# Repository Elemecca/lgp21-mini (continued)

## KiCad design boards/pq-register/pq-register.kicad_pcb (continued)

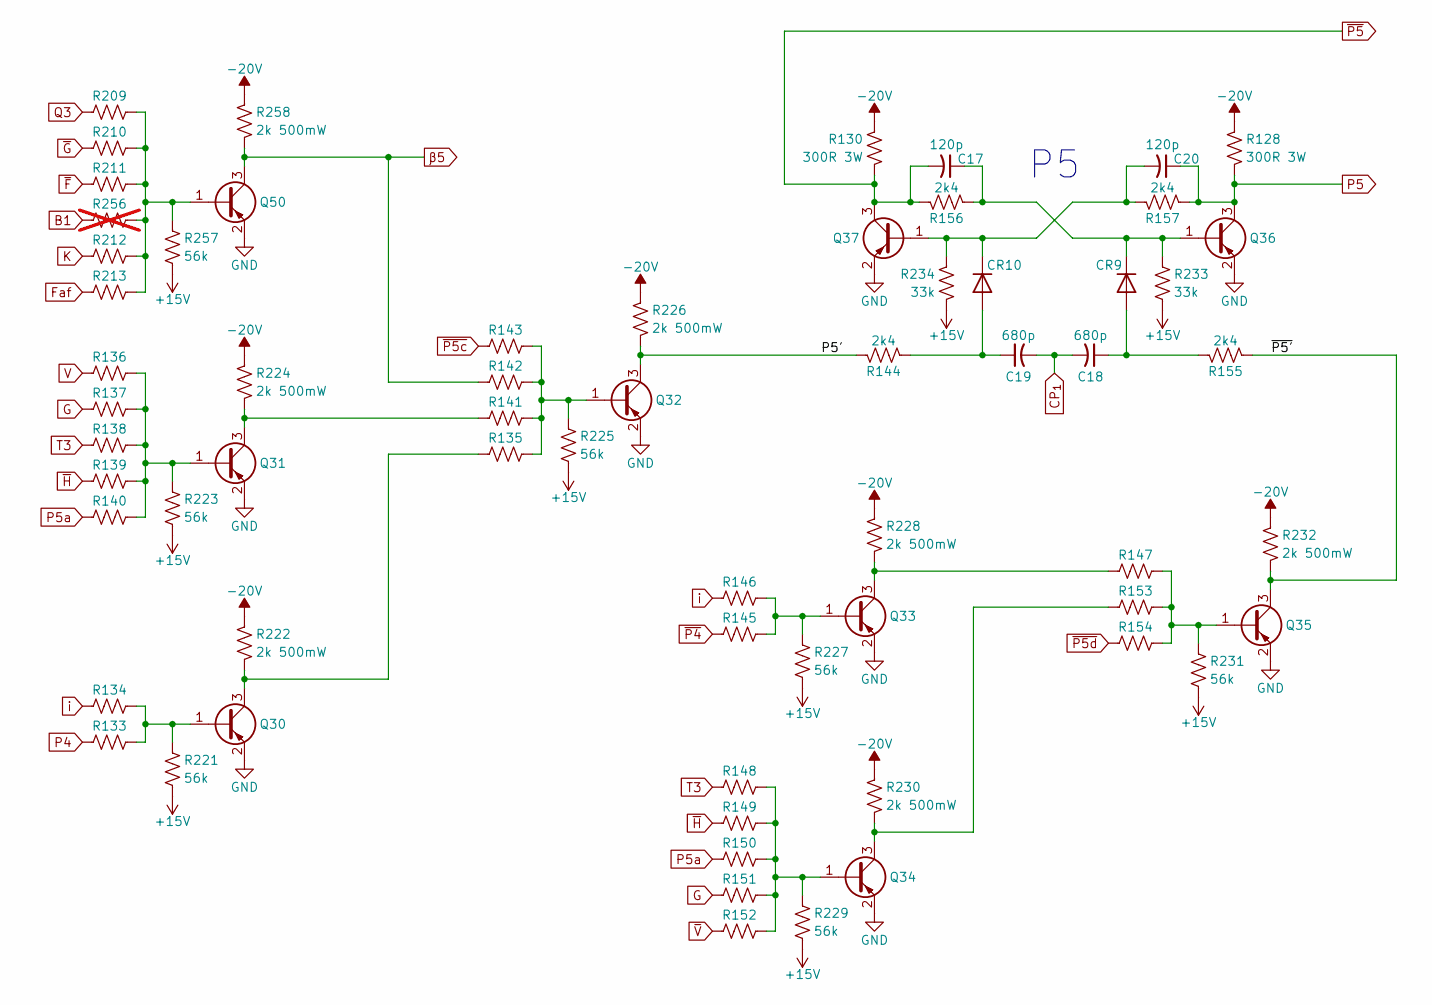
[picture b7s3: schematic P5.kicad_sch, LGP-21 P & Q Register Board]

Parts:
C17, C20: 120p; C_0402_1005Metric
C18, C19: 680p; C_0402_1005Metric
CR9, CR10: 1N5819WS; D_SOD-323
Q30, Q31, Q32, Q33, Q34, Q35, Q36, Q37, Q50: MMBT5401; SOT-23
R128, R130: 300R 3W; R_Axial_DIN0516_L15.5mm_D5.0mm_P20.32mm_Horizontal
R133, R134, R135, R136, R137, R138, R139, R140, R141, R142, R143, R145, R146, R147, R148, R149, R150, R151, R152, R153, R154, R209, R210, R211, R212, R213: 15k; R_0402_1005Metric
R144, R155, R156, R157: 2k4; R_0402_1005Metric
R221, R223, R225, R227, R229, R231, R257: 56k; R_0402_1005Metric
R222, R224, R226, R228, R230, R232, R258: 2k 500mW; R_1210_3225Metric
R233, R234: 33k; R_0402_1005Metric
R256: 15k; R_0402_1005Metric; not fitted

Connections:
+15V: R221.2, R223.2, R225.2, R227.2, R229.2, R231.2, R233.2, R234.2, R257.2; also elsewhere on the board
-20V: R128.1, R130.1, R222.1, R224.1, R226.1, R228.1, R230.1, R232.1, R258.1; also elsewhere on the board
/P5/P5': Q32.3 (C), R144.1, R226.2
/P5/~P5': Q35.3 (C), R155.2, R232.2
B1: R256.1; also elsewhere on the board
CP_{1}: C18.2, C19.2; also elsewhere on the board
Faf: R213.1; also elsewhere on the board
G: R137.1, R151.1; also elsewhere on the board
GND: Q30.2 (E), Q31.2 (E), Q32.2 (E), Q33.2 (E), Q34.2 (E), Q35.2 (E), Q36.2 (E), Q37.2 (E), Q50.2 (E); also elsewhere on the board
K: R212.1; also elsewhere on the board
unnamed: C18.1, CR9.2 (A), R155.1
unnamed: C17.1, CR9.1 (K), Q36.1 (B), R156.2, R233.1
unnamed: C19.1, CR10.2 (A), R144.2
unnamed: C20.2, CR10.1 (K), Q37.1 (B), R157.1, R234.1
unnamed: Q30.1 (B), R133.2, R134.2, R221.1
unnamed: Q30.3 (C), R135.1, R222.2
unnamed: Q31.1 (B), R136.2, R137.2, R138.2, R139.2, R140.2, R223.1
unnamed: Q31.3 (C), R141.1, R224.2
unnamed: Q32.1 (B), R135.2, R141.2, R142.2, R143.2, R225.1
unnamed: Q33.1 (B), R145.2, R146.2, R227.1
unnamed: Q33.3 (C), R147.1, R228.2
unnamed: Q34.1 (B), R148.2, R149.2, R150.2, R151.2, R152.2, R229.1
unnamed: Q34.3 (C), R153.1, R230.2
unnamed: Q35.1 (B), R147.2, R153.2, R154.2, R231.1
unnamed: Q50.1 (B), R209.2, R210.2, R211.2, R212.2, R213.2, R256.2, R257.1
P4: R133.1; also elsewhere on the board
P5: C20.1, Q36.3 (C), R128.2, R157.2; also elsewhere on the board
P5a: R140.1, R150.1; also elsewhere on the board
Q3: R209.1; also elsewhere on the board
T3: R138.1, R148.1; also elsewhere on the board
V: R136.1; also elsewhere on the board
i: R134.1, R146.1; also elsewhere on the board
~F: R211.1; also elsewhere on the board
~G: R210.1; also elsewhere on the board
~H: R139.1, R149.1; also elsewhere on the board
~P4: R145.1; also elsewhere on the board
~P5c: R143.1; also elsewhere on the board
~P5d: R154.1; also elsewhere on the board
~P5: C17.2, Q37.3 (C), R130.2, R156.1; also elsewhere on the board
~V: R152.1; also elsewhere on the board
β5: Q50.3 (C), R142.1, R258.2

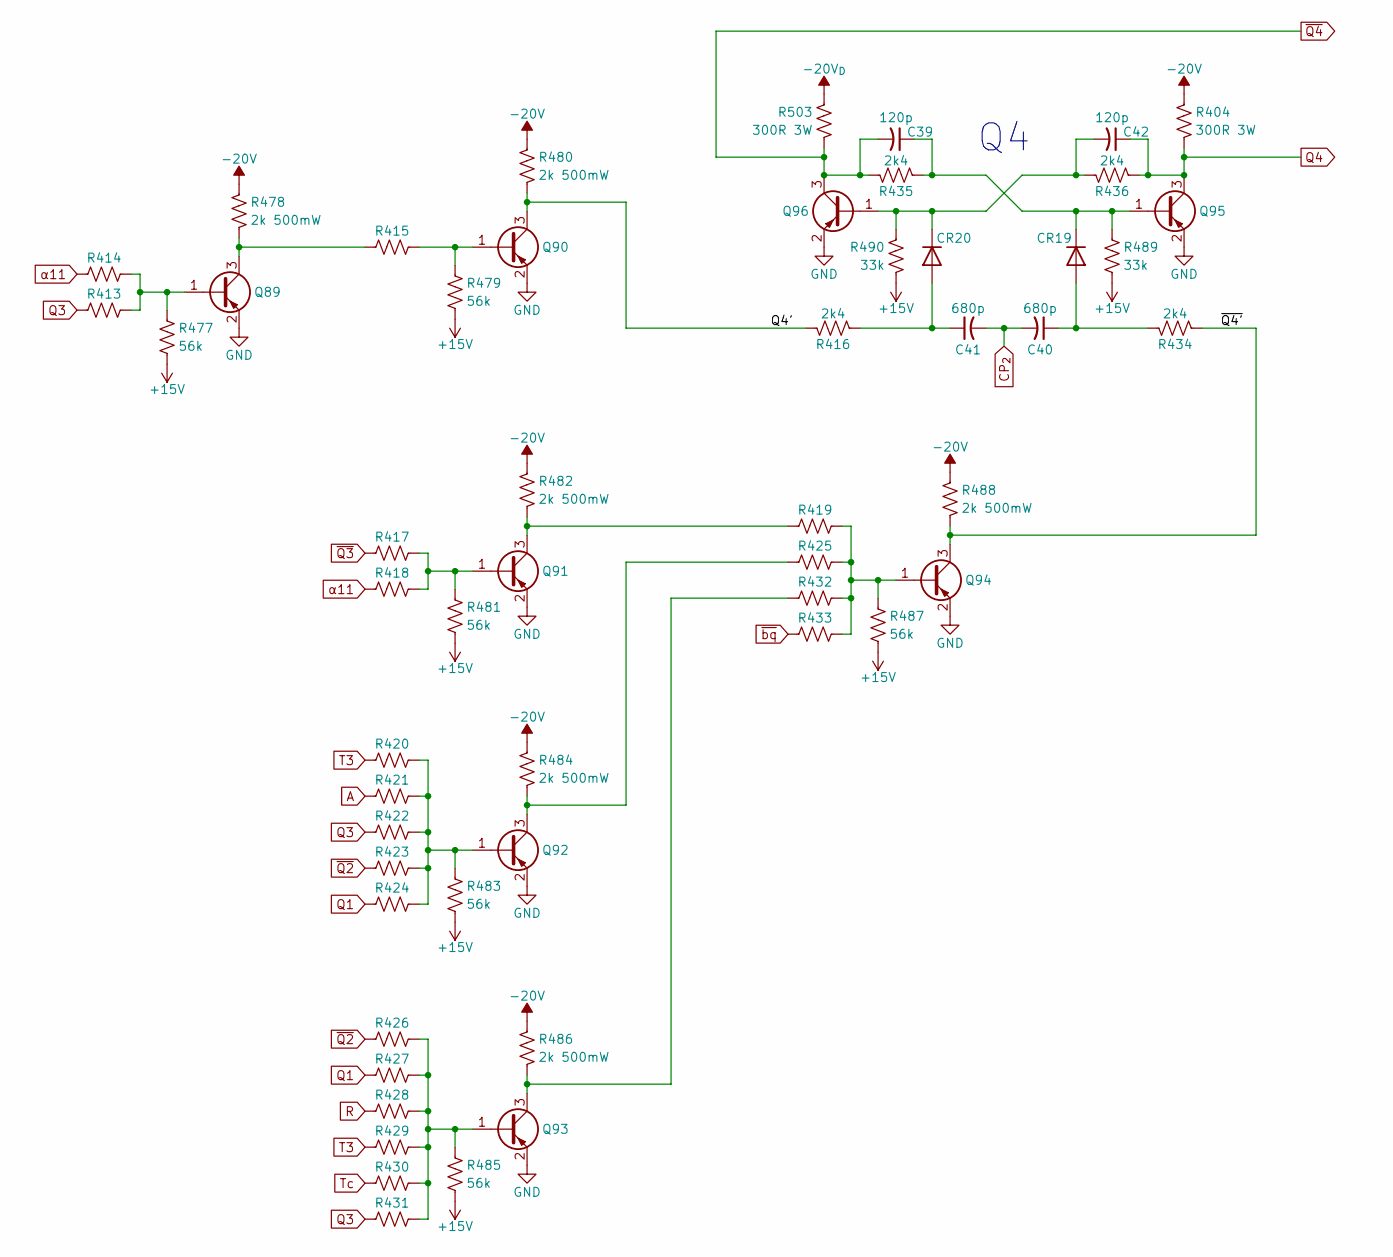
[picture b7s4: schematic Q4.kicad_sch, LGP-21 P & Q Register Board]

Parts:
C39, C42: 120p; C_0402_1005Metric
C40, C41: 680p; C_0402_1005Metric
CR19, CR20: 1N5819WS; D_SOD-323
Q89, Q90, Q91, Q92, Q93, Q94, Q95, Q96: MMBT5401; SOT-23
R404, R503: 300R 3W; R_Axial_DIN0516_L15.5mm_D5.0mm_P20.32mm_Horizontal
R413, R414, R415, R417, R418, R419, R420, R421, R422, R423, R424, R425, R426, R427, R428, R429, R430, R431, R432, R433: 15k; R_0402_1005Metric
R416, R434, R435, R436: 2k4; R_0402_1005Metric
R477, R479, R481, R483, R485, R487: 56k; R_0402_1005Metric
R478, R480, R482, R484, R486, R488: 2k 500mW; R_1210_3225Metric
R489, R490: 33k; R_0402_1005Metric

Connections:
+15V: R477.2, R479.2, R481.2, R483.2, R485.2, R487.2, R489.2, R490.2; also elsewhere on the board
-20V: R404.1, R478.1, R480.1, R482.1, R484.1, R486.1, R488.1; also elsewhere on the board
-20V_{D}: R503.1; also elsewhere on the board
/Q4/Q4': Q90.3 (C), R416.1, R480.2
/Q4/~Q4': Q94.3 (C), R434.2, R488.2
A: R421.1; also elsewhere on the board
CP_{2}: C40.2, C41.2; also elsewhere on the board
GND: Q89.2 (E), Q90.2 (E), Q91.2 (E), Q92.2 (E), Q93.2 (E), Q94.2 (E), Q95.2 (E), Q96.2 (E); also elsewhere on the board
unnamed: C40.1, CR19.2 (A), R434.1
unnamed: C39.1, CR19.1 (K), Q95.1 (B), R435.2, R489.1
unnamed: C41.1, CR20.2 (A), R416.2
unnamed: C42.2, CR20.1 (K), Q96.1 (B), R436.1, R490.1
unnamed: Q89.1 (B), R413.2, R414.2, R477.1
unnamed: Q89.3 (C), R415.1, R478.2
unnamed: Q90.1 (B), R415.2, R479.1
unnamed: Q91.1 (B), R417.2, R418.2, R481.1
unnamed: Q91.3 (C), R419.1, R482.2
unnamed: Q92.1 (B), R420.2, R421.2, R422.2, R423.2, R424.2, R483.1
unnamed: Q92.3 (C), R425.1, R484.2
unnamed: Q93.1 (B), R426.2, R427.2, R428.2, R429.2, R430.2, R431.2, R485.1
unnamed: Q93.3 (C), R432.1, R486.2
unnamed: Q94.1 (B), R419.2, R425.2, R432.2, R433.2, R487.1
Q1: R424.1, R427.1; also elsewhere on the board
Q3: R413.1, R422.1, R431.1; also elsewhere on the board
Q4: C42.1, Q95.3 (C), R404.2, R436.2; also elsewhere on the board
R: R428.1; also elsewhere on the board
T3: R420.1, R429.1; also elsewhere on the board
Tc: R430.1; also elsewhere on the board
~Q2: R423.1, R426.1; also elsewhere on the board
~Q3: R417.1; also elsewhere on the board
~Q4: C39.2, Q96.3 (C), R435.1, R503.2; also elsewhere on the board
~bq: R433.1; also elsewhere on the board
α11: R414.1, R418.1; also elsewhere on the board

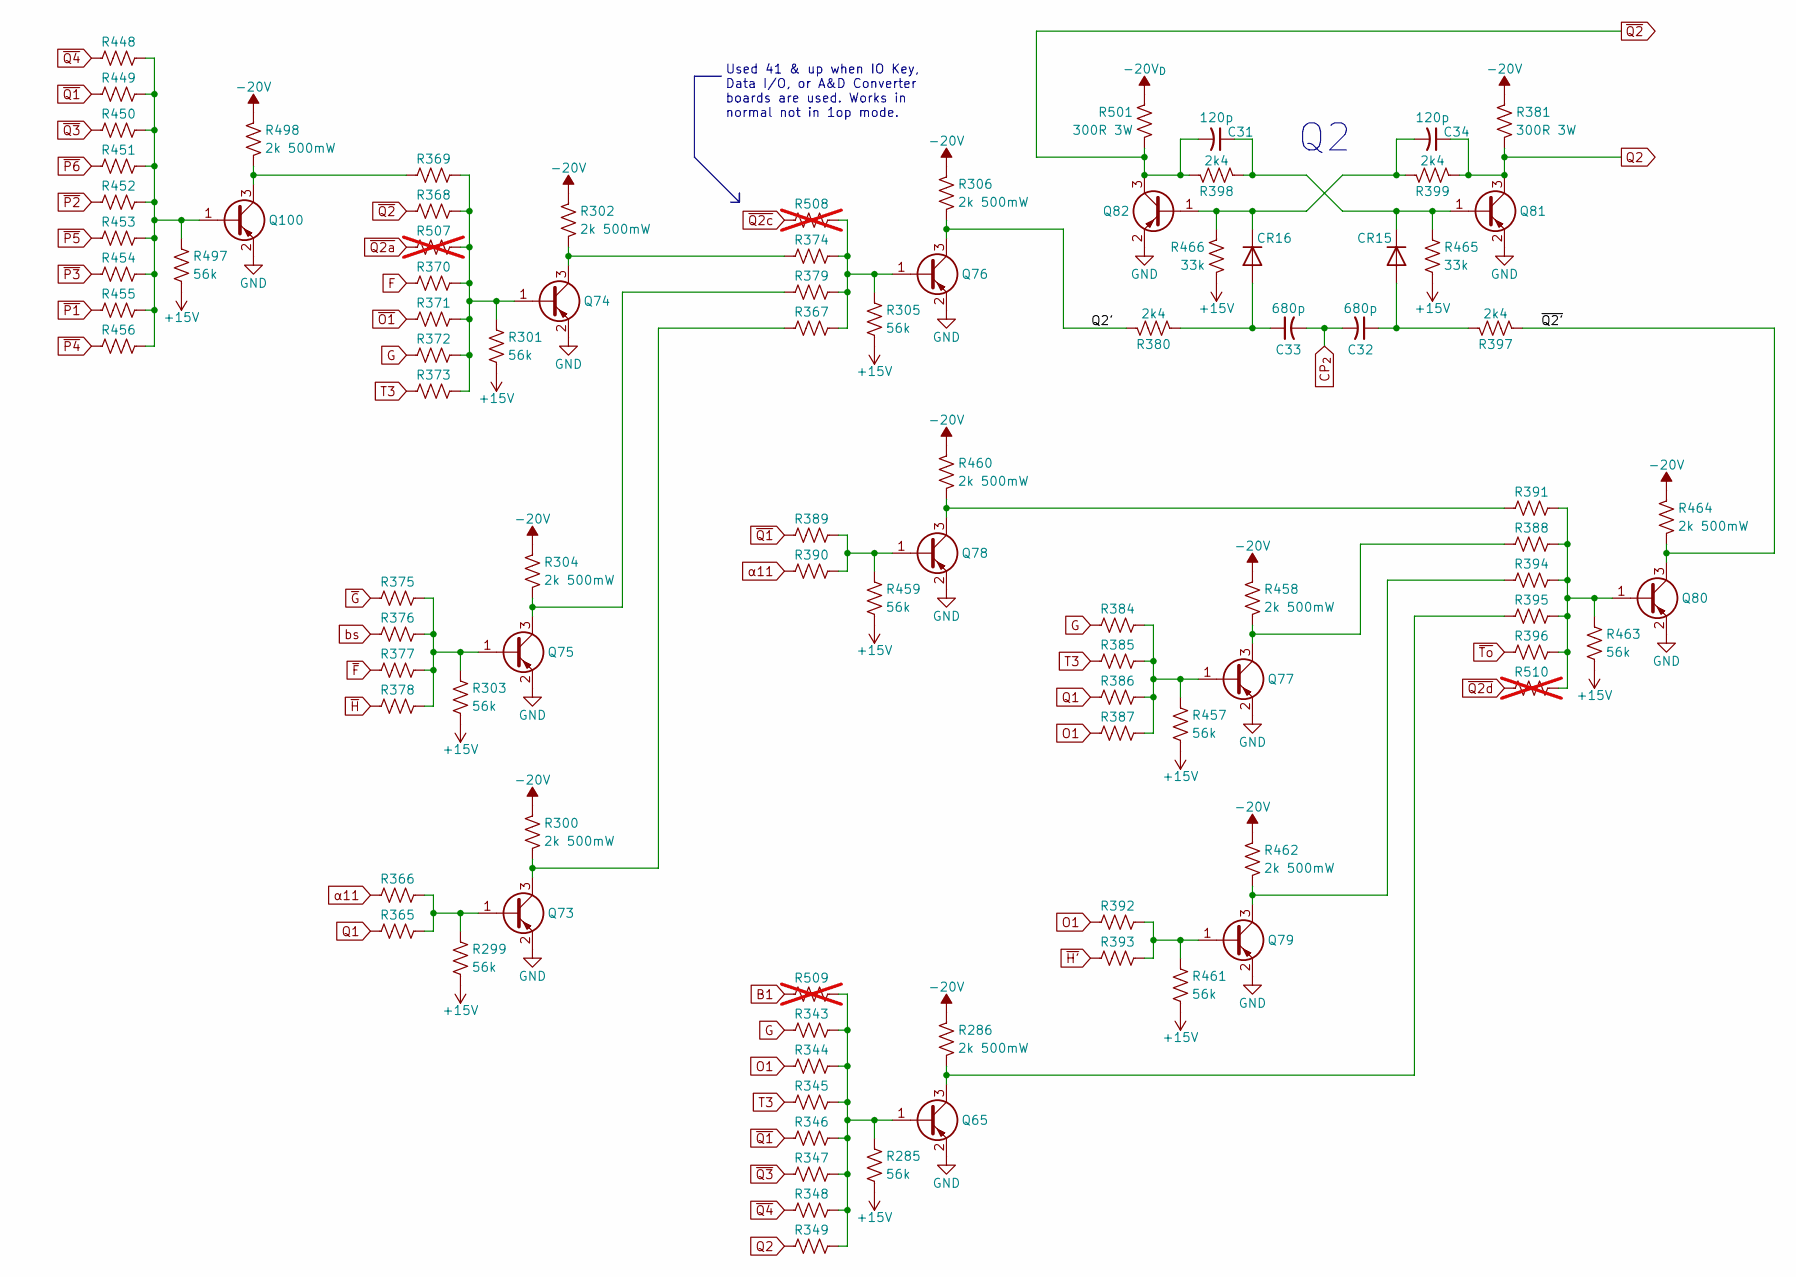
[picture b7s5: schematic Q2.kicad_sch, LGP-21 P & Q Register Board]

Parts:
C31, C34: 120p; C_0402_1005Metric
C32, C33: 680p; C_0402_1005Metric
CR15, CR16: 1N5819WS; D_SOD-323
Q65, Q73, Q74, Q75, Q76, Q77, Q78, Q79, Q80, Q81, Q82, Q100: MMBT5401; SOT-23
R285, R299, R301, R303, R305, R457, R459, R461, R463, R497: 56k; R_0402_1005Metric
R286, R300, R302, R304, R306, R458, R460, R462, R464, R498: 2k 500mW; R_1210_3225Metric
R343, R344, R345, R346, R347, R348, R349, R365, R366, R367, R368, R369, R370, R371, R372, R373, R374, R375, R376, R377, R378, R379, R384, R385, R386, R387, R388, R389, R390, R391, R392, R393, R394, R395, R396, R448, R449, R450, R451, R452, R453, R454, R455, R456: 15k; R_0402_1005Metric
R380, R397, R398, R399: 2k4; R_0402_1005Metric
R381, R501: 300R 3W; R_Axial_DIN0516_L15.5mm_D5.0mm_P20.32mm_Horizontal
R465, R466: 33k; R_0402_1005Metric
R507, R508, R509, R510: 15k; R_0402_1005Metric; not fitted

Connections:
+15V: R285.2, R299.2, R301.2, R303.2, R305.2, R457.2, R459.2, R461.2, R463.2, R465.2, R466.2, R497.2; also elsewhere on the board
-20V: R286.1, R300.1, R302.1, R304.1, R306.1, R381.1, R458.1, R460.1, R462.1, R464.1, R498.1; also elsewhere on the board
-20V_{D}: R501.1; also elsewhere on the board
/Q2/Q2': Q76.3 (C), R306.2, R380.1
/Q2/~Q2': Q80.3 (C), R397.2, R464.2
B1: R509.1; also elsewhere on the board
CP_{2}: C32.2, C33.2; also elsewhere on the board
F: R370.1; also elsewhere on the board
G: R343.1, R372.1, R384.1; also elsewhere on the board
GND: Q65.2 (E), Q73.2 (E), Q74.2 (E), Q75.2 (E), Q76.2 (E), Q77.2 (E), Q78.2 (E), Q79.2 (E), Q80.2 (E), Q81.2 (E), Q82.2 (E), Q100.2 (E); also elsewhere on the board
unnamed: C32.1, CR15.2 (A), R397.1
unnamed: C31.1, CR15.1 (K), Q81.1 (B), R398.2, R465.1
unnamed: C33.1, CR16.2 (A), R380.2
unnamed: C34.2, CR16.1 (K), Q82.1 (B), R399.1, R466.1
unnamed: Q65.1 (B), R285.1, R343.2, R344.2, R345.2, R346.2, R347.2, R348.2, R349.2, R509.2
unnamed: Q65.3 (C), R286.2, R395.1
unnamed: Q73.1 (B), R299.1, R365.2, R366.2
unnamed: Q73.3 (C), R300.2, R367.1
unnamed: Q74.1 (B), R301.1, R368.2, R369.2, R370.2, R371.2, R372.2, R373.2, R507.2
unnamed: Q74.3 (C), R302.2, R374.1
unnamed: Q75.1 (B), R303.1, R375.2, R376.2, R377.2, R378.2
unnamed: Q75.3 (C), R304.2, R379.1
unnamed: Q76.1 (B), R305.1, R367.2, R374.2, R379.2, R508.2
unnamed: Q77.1 (B), R384.2, R385.2, R386.2, R387.2, R457.1
unnamed: Q77.3 (C), R388.1, R458.2
unnamed: Q78.1 (B), R389.2, R390.2, R459.1
unnamed: Q78.3 (C), R391.1, R460.2
unnamed: Q79.1 (B), R392.2, R393.2, R461.1
unnamed: Q79.3 (C), R394.1, R462.2
unnamed: Q80.1 (B), R388.2, R391.2, R394.2, R395.2, R396.2, R463.1, R510.2
unnamed: Q100.1 (B), R448.2, R449.2, R450.2, R451.2, R452.2, R453.2, R454.2, R455.2, R456.2, R497.1
unnamed: Q100.3 (C), R369.1, R498.2
O1: R344.1, R387.1, R392.1; also elsewhere on the board
Q1: R365.1, R386.1; also elsewhere on the board
Q2: C34.1, Q81.3 (C), R349.1, R381.2, R399.2; also elsewhere on the board
T3: R345.1, R373.1, R385.1; also elsewhere on the board
bs: R376.1; also elsewhere on the board
~F: R377.1; also elsewhere on the board
~G: R375.1; also elsewhere on the board
~H': R393.1; also elsewhere on the board
~H: R378.1; also elsewhere on the board
~O1: R371.1; also elsewhere on the board
~P1: R455.1; also elsewhere on the board
~P2: R452.1; also elsewhere on the board
~P3: R454.1; also elsewhere on the board
~P4: R456.1; also elsewhere on the board
~P5: R453.1; also elsewhere on the board
~P6: R451.1; also elsewhere on the board
~Q1: R346.1, R389.1, R449.1; also elsewhere on the board
~Q2a: R507.1
~Q2c: R508.1; also elsewhere on the board
~Q2d: R510.1; also elsewhere on the board
~Q2: C31.2, Q82.3 (C), R368.1, R398.1, R501.2; also elsewhere on the board
~Q3: R347.1, R450.1; also elsewhere on the board
~Q4: R348.1, R448.1; also elsewhere on the board
~To: R396.1; also elsewhere on the board
α11: R366.1, R390.1; also elsewhere on the board

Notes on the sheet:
Used 41 & up when IO Key, Data I/O, or A&D Converter boards are used. Works in normal not in 1op mode.

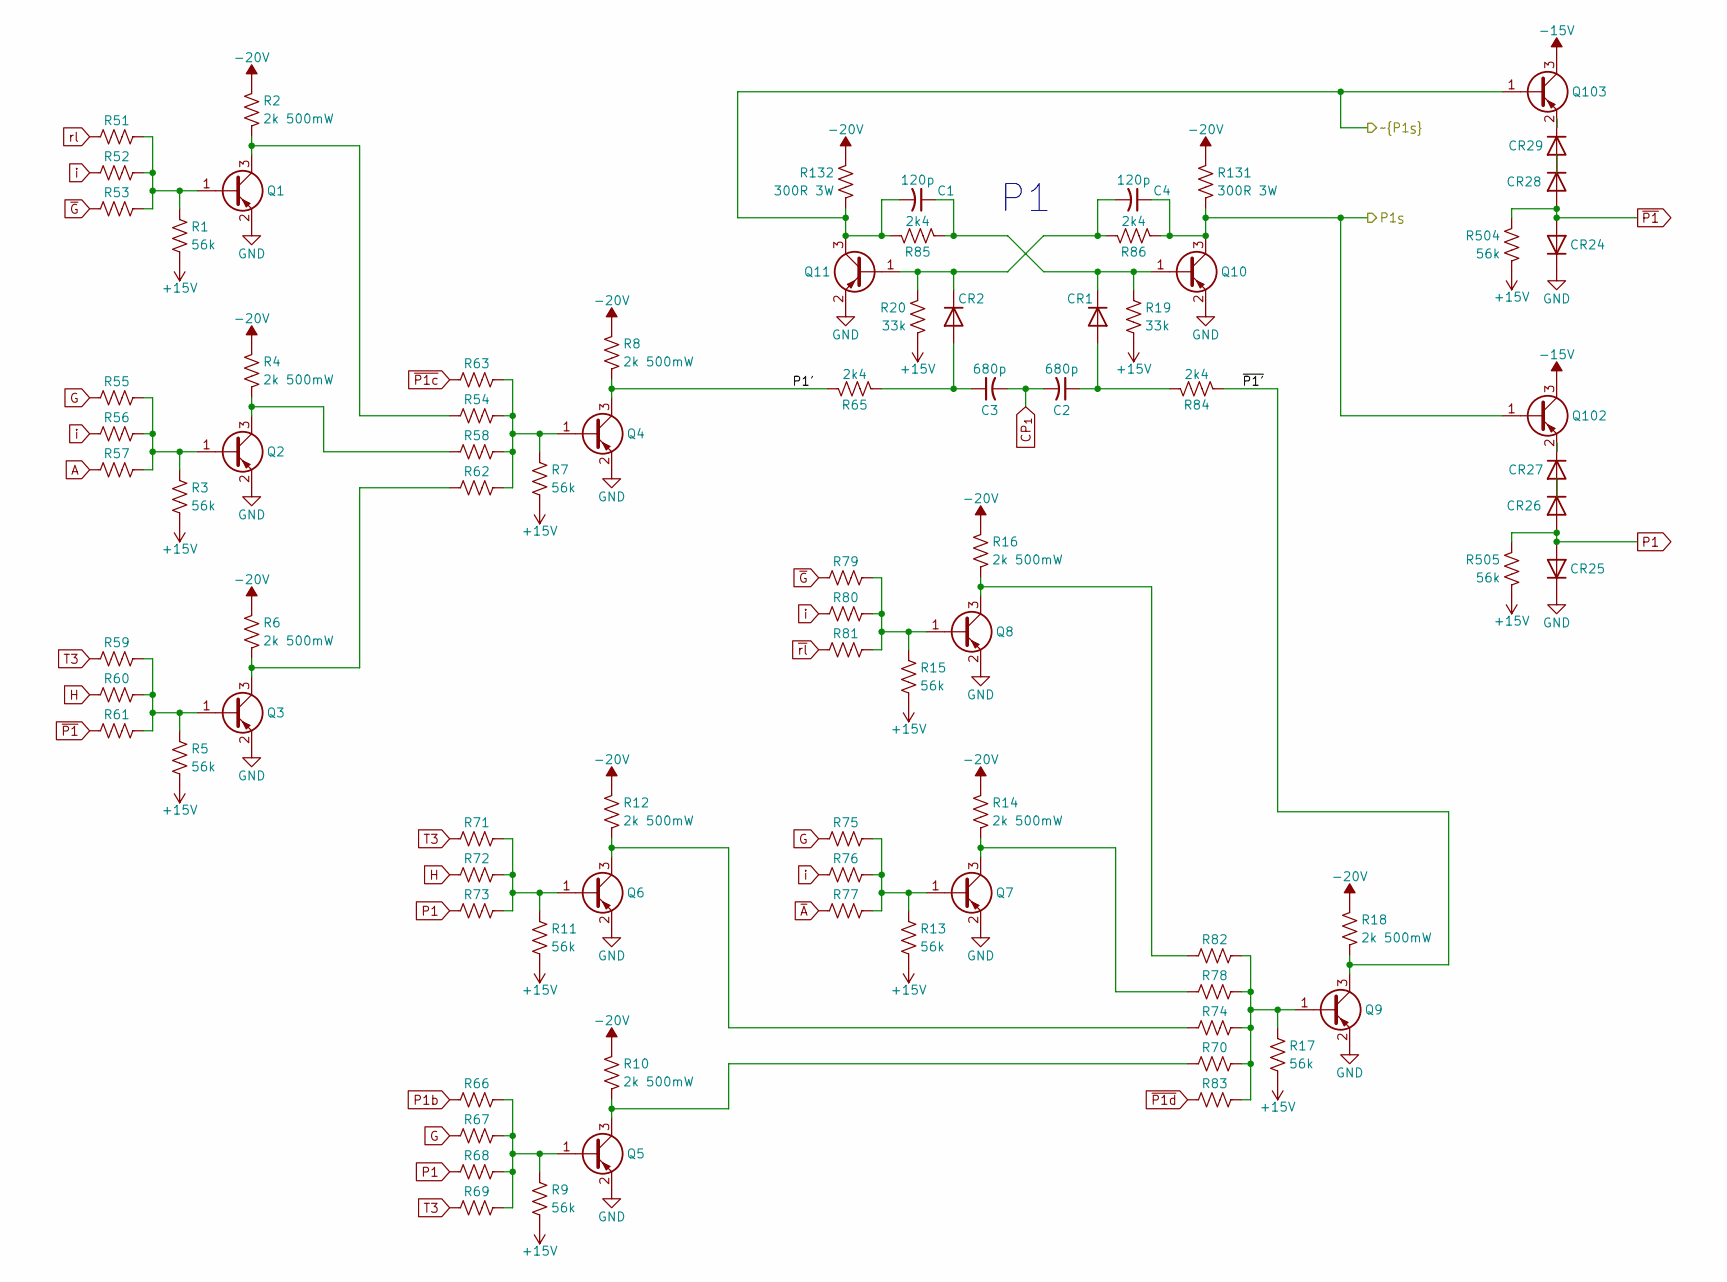
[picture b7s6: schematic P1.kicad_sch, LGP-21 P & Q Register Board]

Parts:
C1, C4: 120p; C_0402_1005Metric
C2, C3: 680p; C_0402_1005Metric
CR1, CR2, CR24, CR25, CR26, CR27, CR28, CR29: 1N5819WS; D_SOD-323
Q1, Q2, Q3, Q4, Q5, Q6, Q7, Q8, Q9, Q10, Q11, Q102, Q103: MMBT5401; SOT-23
R1, R3, R5, R7, R9, R11, R13, R15, R17, R504, R505: 56k; R_0402_1005Metric
R2, R4, R6, R8, R10, R12, R14, R16, R18: 2k 500mW; R_1210_3225Metric
R19, R20: 33k; R_0402_1005Metric
R51, R52, R53, R54, R55, R56, R57, R58, R59, R60, R61, R62, R63, R66, R67, R68, R69, R70, R71, R72, R73, R74, R75, R76, R77, R78, R79, R80, R81, R82, R83: 15k; R_0402_1005Metric
R65, R84, R85, R86: 2k4; R_0402_1005Metric
R131, R132: 300R 3W; R_Axial_DIN0516_L15.5mm_D5.0mm_P20.32mm_Horizontal

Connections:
+15V: R1.2, R3.2, R5.2, R7.2, R9.2, R11.2, R13.2, R15.2, R17.2, R19.2, R20.2, R504.2, R505.2; also elsewhere on the board
-15V: Q102.3 (C), Q103.3 (C); also elsewhere on the board
-20V: R2.1, R4.1, R6.1, R8.1, R10.1, R12.1, R14.1, R16.1, R18.1, R131.1, R132.1; also elsewhere on the board
/P1/P1': Q4.3 (C), R8.2, R65.1
/P1/P1_{S}: C4.1, Q10.3 (C), Q102.1 (B), R86.2, R131.2; also elsewhere on the board
/P1/~P1': Q9.3 (C), R18.2, R84.2
/P1/~P1_{S}: C1.2, Q11.3 (C), Q103.1 (B), R85.1, R132.2; also elsewhere on the board
A: R57.1; also elsewhere on the board
CP_{1}: C2.2, C3.2; also elsewhere on the board
G: R55.1, R67.1, R75.1; also elsewhere on the board
GND: CR24.1 (K), CR25.1 (K), Q1.2 (E), Q2.2 (E), Q3.2 (E), Q4.2 (E), Q5.2 (E), Q6.2 (E), Q7.2 (E), Q8.2 (E), Q9.2 (E), Q10.2 (E), Q11.2 (E); also elsewhere on the board
H: R60.1, R72.1; also elsewhere on the board
unnamed: C2.1, CR1.2 (A), R84.1
unnamed: C1.1, CR1.1 (K), Q10.1 (B), R19.1, R85.2
unnamed: C3.1, CR2.2 (A), R65.2
unnamed: C4.2, CR2.1 (K), Q11.1 (B), R20.1, R86.1
unnamed: CR26.1 (K), CR27.2 (A)
unnamed: CR27.1 (K), Q102.2 (E)
unnamed: CR28.1 (K), CR29.2 (A)
unnamed: CR29.1 (K), Q103.2 (E)
unnamed: Q1.1 (B), R1.1, R51.2, R52.2, R53.2
unnamed: Q1.3 (C), R2.2, R54.1
unnamed: Q2.1 (B), R3.1, R55.2, R56.2, R57.2
unnamed: Q2.3 (C), R4.2, R58.1
unnamed: Q3.1 (B), R5.1, R59.2, R60.2, R61.2
unnamed: Q3.3 (C), R6.2, R62.1
unnamed: Q4.1 (B), R7.1, R54.2, R58.2, R62.2, R63.2
unnamed: Q5.1 (B), R9.1, R66.2, R67.2, R68.2, R69.2
unnamed: Q5.3 (C), R10.2, R70.1
unnamed: Q6.1 (B), R11.1, R71.2, R72.2, R73.2
unnamed: Q6.3 (C), R12.2, R74.1
unnamed: Q7.1 (B), R13.1, R75.2, R76.2, R77.2
unnamed: Q7.3 (C), R14.2, R78.1
unnamed: Q8.1 (B), R15.1, R79.2, R80.2, R81.2
unnamed: Q8.3 (C), R16.2, R82.1
unnamed: Q9.1 (B), R17.1, R70.2, R74.2, R78.2, R82.2, R83.2
P1: CR25.2 (A), CR26.2 (A), R68.1, R73.1, R505.1; also elsewhere on the board
P1b: R66.1; also elsewhere on the board
T3: R59.1, R69.1, R71.1; also elsewhere on the board
i: R52.1, R56.1, R76.1, R80.1; also elsewhere on the board
rl: R51.1; also elsewhere on the board
~A: R77.1; also elsewhere on the board
~G: R53.1, R79.1; also elsewhere on the board
~P1c: R63.1; also elsewhere on the board
~P1d: R83.1; also elsewhere on the board
~P1: CR24.2 (A), CR28.2 (A), R61.1, R504.1; also elsewhere on the board
~rl: R81.1; also elsewhere on the board

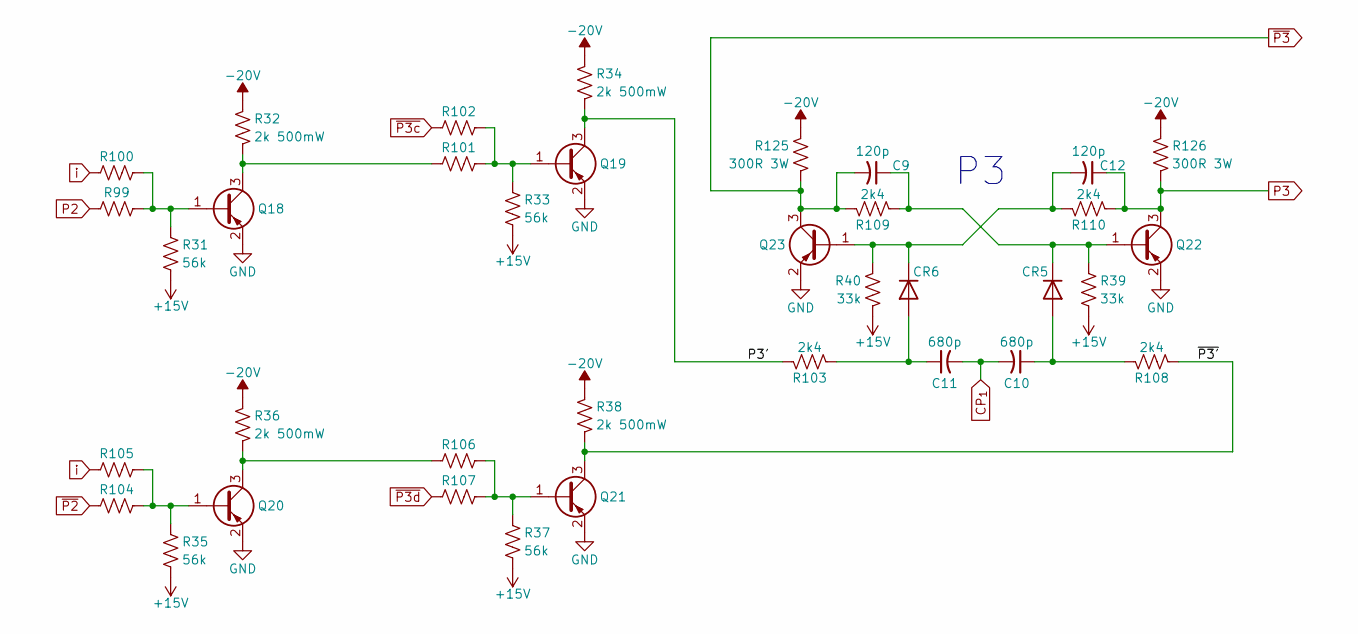
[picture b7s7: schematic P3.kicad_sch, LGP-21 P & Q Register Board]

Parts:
C9, C12: 120p; C_0402_1005Metric
C10, C11: 680p; C_0402_1005Metric
CR5, CR6: 1N5819WS; D_SOD-323
Q18, Q19, Q20, Q21, Q22, Q23: MMBT5401; SOT-23
R31, R33, R35, R37: 56k; R_0402_1005Metric
R32, R34, R36, R38: 2k 500mW; R_1210_3225Metric
R39, R40: 33k; R_0402_1005Metric
R99, R100, R101, R102, R104, R105, R106, R107: 15k; R_0402_1005Metric
R103, R108, R109, R110: 2k4; R_0402_1005Metric
R125, R126: 300R 3W; R_Axial_DIN0516_L15.5mm_D5.0mm_P20.32mm_Horizontal

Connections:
+15V: R31.2, R33.2, R35.2, R37.2, R39.2, R40.2; also elsewhere on the board
-20V: R32.1, R34.1, R36.1, R38.1, R125.1, R126.1; also elsewhere on the board
/P3/P3': Q19.3 (C), R34.2, R103.1
/P3/~P3': Q21.3 (C), R38.2, R108.2
CP_{1}: C10.2, C11.2; also elsewhere on the board
GND: Q18.2 (E), Q19.2 (E), Q20.2 (E), Q21.2 (E), Q22.2 (E), Q23.2 (E); also elsewhere on the board
unnamed: C10.1, CR5.2 (A), R108.1
unnamed: C9.1, CR5.1 (K), Q22.1 (B), R39.1, R109.2
unnamed: C11.1, CR6.2 (A), R103.2
unnamed: C12.2, CR6.1 (K), Q23.1 (B), R40.1, R110.1
unnamed: Q18.1 (B), R31.1, R99.2, R100.2
unnamed: Q18.3 (C), R32.2, R101.1
unnamed: Q19.1 (B), R33.1, R101.2, R102.2
unnamed: Q20.1 (B), R35.1, R104.2, R105.2
unnamed: Q20.3 (C), R36.2, R106.1
unnamed: Q21.1 (B), R37.1, R106.2, R107.2
P2: R99.1; also elsewhere on the board
P3: C12.1, Q22.3 (C), R110.2, R126.2; also elsewhere on the board
i: R100.1, R105.1; also elsewhere on the board
~P2: R104.1; also elsewhere on the board
~P3c: R102.1; also elsewhere on the board
~P3d: R107.1; also elsewhere on the board
~P3: C9.2, Q23.3 (C), R109.1, R125.2; also elsewhere on the board

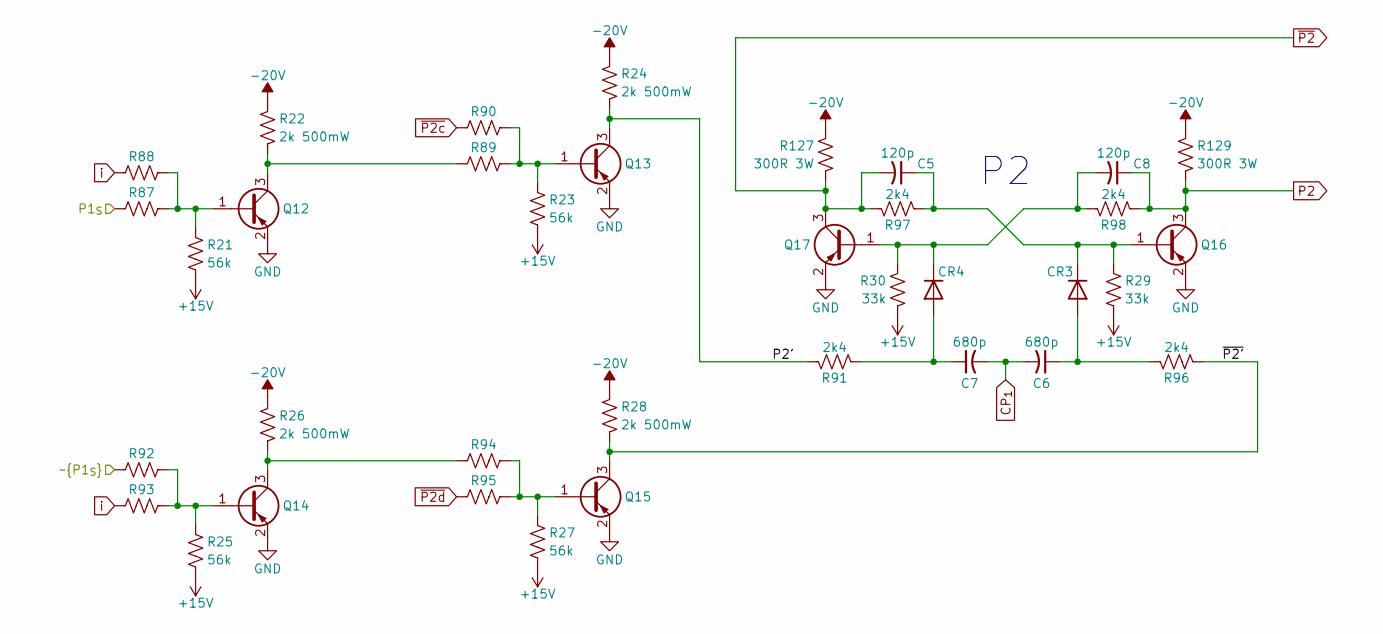
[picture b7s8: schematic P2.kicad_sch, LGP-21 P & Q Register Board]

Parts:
C5, C8: 120p; C_0402_1005Metric
C6, C7: 680p; C_0402_1005Metric
CR3, CR4: 1N5819WS; D_SOD-323
Q12, Q13, Q14, Q15, Q16, Q17: MMBT5401; SOT-23
R21, R23, R25, R27: 56k; R_0402_1005Metric
R22, R24, R26, R28: 2k 500mW; R_1210_3225Metric
R29, R30: 33k; R_0402_1005Metric
R87, R88, R89, R90, R92, R93, R94, R95: 15k; R_0402_1005Metric
R91, R96, R97, R98: 2k4; R_0402_1005Metric
R127, R129: 300R 3W; R_Axial_DIN0516_L15.5mm_D5.0mm_P20.32mm_Horizontal

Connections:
+15V: R21.2, R23.2, R25.2, R27.2, R29.2, R30.2; also elsewhere on the board
-20V: R22.1, R24.1, R26.1, R28.1, R127.1, R129.1; also elsewhere on the board
/P1/P1_{S}: R87.1; also elsewhere on the board
/P1/~P1_{S}: R92.1; also elsewhere on the board
/P2/P2': Q13.3 (C), R24.2, R91.1
/P2/~P2': Q15.3 (C), R28.2, R96.2
CP_{1}: C6.2, C7.2; also elsewhere on the board
GND: Q12.2 (E), Q13.2 (E), Q14.2 (E), Q15.2 (E), Q16.2 (E), Q17.2 (E); also elsewhere on the board
unnamed: C6.1, CR3.2 (A), R96.1
unnamed: C5.1, CR3.1 (K), Q16.1 (B), R29.1, R97.2
unnamed: C7.1, CR4.2 (A), R91.2
unnamed: C8.2, CR4.1 (K), Q17.1 (B), R30.1, R98.1
unnamed: Q12.1 (B), R21.1, R87.2, R88.2
unnamed: Q12.3 (C), R22.2, R89.1
unnamed: Q13.1 (B), R23.1, R89.2, R90.2
unnamed: Q14.1 (B), R25.1, R92.2, R93.2
unnamed: Q14.3 (C), R26.2, R94.1
unnamed: Q15.1 (B), R27.1, R94.2, R95.2
P2: C8.1, Q16.3 (C), R98.2, R129.2; also elsewhere on the board
i: R88.1, R93.1; also elsewhere on the board
~P2c: R90.1; also elsewhere on the board
~P2d: R95.1; also elsewhere on the board
~P2: C5.2, Q17.3 (C), R97.1, R127.2; also elsewhere on the board

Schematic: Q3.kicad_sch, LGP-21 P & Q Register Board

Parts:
C35, C38: 120p; C_0402_1005Metric
C36, C37: 680p; C_0402_1005Metric
CR17, CR18, CR21, CR22, CR23: 1N5819WS; D_SOD-323
Q63, Q83, Q84, Q85, Q86, Q87, Q88, Q101: MMBT5401; SOT-23
R281, R467, R469, R471, R473, R499: 56k; R_0402_1005Metric
R282, R468, R470, R472, R474: 2k 500mW; R_1210_3225Metric
R334, R335, R336, R337, R338, R339, R400, R401, R402, R403, R406, R407, R408, R409: 15k; R_0402_1005Metric
R383, R500: 300R 3W; R_Axial_DIN0516_L15.5mm_D5.0mm_P20.32mm_Horizontal
R405, R410, R411, R412: 2k4; R_0402_1005Metric
R475, R476: 33k; R_0402_1005Metric
R511: 15k; R_0402_1005Metric; not fitted

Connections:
+15V: R281.2, R467.2, R469.2, R471.2, R473.2, R475.2, R476.2, R499.2; also elsewhere on the board
-15V: Q101.3 (C); also elsewhere on the board
-20V: R282.1, R383.1, R468.1, R470.1, R472.1, R474.1; also elsewhere on the board
-20V_{D}: R500.1; also elsewhere on the board
/Q3/Q3': Q84.3 (C), R405.1, R470.2
/Q3/~Q3': Q86.3 (C), R410.2, R474.2
/Q3/~Q3_{S}: C35.2, Q88.3 (C), Q101.1 (B), R411.1, R500.2
CP_{2}: C36.2, C37.2; also elsewhere on the board
G: R338.1; also elsewhere on the board
GND: CR21.1 (K), Q63.2 (E), Q83.2 (E), Q84.2 (E), Q85.2 (E), Q86.2 (E), Q87.2 (E), Q88.2 (E); also elsewhere on the board
unnamed: C36.1, CR17.2 (A), R410.1
unnamed: C35.1, CR17.1 (K), Q87.1 (B), R411.2, R475.1
unnamed: C37.1, CR18.2 (A), R405.2
unnamed: C38.2, CR18.1 (K), Q88.1 (B), R412.1, R476.1
unnamed: CR22.1 (K), CR23.2 (A)
unnamed: CR23.1 (K), Q101.2 (E)
unnamed: Q63.1 (B), R281.1, R334.2, R335.2, R336.2, R337.2, R338.2, R339.2, R511.2
unnamed: Q63.3 (C), R282.2, R403.1
unnamed: Q83.1 (B), R400.2, R401.2, R467.1
unnamed: Q83.3 (C), R402.1, R468.2
unnamed: Q84.1 (B), R402.2, R403.2, R469.1
unnamed: Q85.1 (B), R406.2, R407.2, R471.1
unnamed: Q85.3 (C), R408.1, R472.2
unnamed: Q86.1 (B), R408.2, R409.2, R473.1
Q1: R339.1; also elsewhere on the board
Q2: R400.1; also elsewhere on the board
Q3: C38.1, Q87.3 (C), R383.2, R412.2; also elsewhere on the board
T3: R336.1; also elsewhere on the board
~Q2: R335.1, R406.1; also elsewhere on the board
~Q3: CR21.2 (A), CR22.2 (A), R337.1, R499.1; also elsewhere on the board
~Q4: R334.1; also elsewhere on the board
~bq: R409.1; also elsewhere on the board
α11: R401.1, R407.1; also elsewhere on the board

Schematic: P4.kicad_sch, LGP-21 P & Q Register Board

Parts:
C13, C16: 120p; C_0402_1005Metric
C14, C15: 680p; C_0402_1005Metric
CR7, CR8: 1N5819WS; D_SOD-323
Q24, Q25, Q26, Q27, Q28, Q29: MMBT5401; SOT-23
R41, R43, R45, R47: 56k; R_0402_1005Metric
R42, R44, R46, R48: 2k 500mW; R_1210_3225Metric
R49, R50: 33k; R_0402_1005Metric
R111, R112, R113, R114, R116, R117, R118, R119: 15k; R_0402_1005Metric
R115, R120, R121, R122: 2k4; R_0402_1005Metric
R123, R124: 300R 3W; R_Axial_DIN0516_L15.5mm_D5.0mm_P20.32mm_Horizontal

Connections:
+15V: R41.2, R43.2, R45.2, R47.2, R49.2, R50.2; also elsewhere on the board
-20V: R42.1, R44.1, R46.1, R48.1, R123.1, R124.1; also elsewhere on the board
/P4/P4': Q25.3 (C), R44.2, R115.1
/P4/~P4': Q27.3 (C), R48.2, R120.2
CP_{1}: C14.2, C15.2; also elsewhere on the board
GND: Q24.2 (E), Q25.2 (E), Q26.2 (E), Q27.2 (E), Q28.2 (E), Q29.2 (E); also elsewhere on the board
unnamed: C14.1, CR7.2 (A), R120.1
unnamed: C13.1, CR7.1 (K), Q28.1 (B), R49.1, R121.2
unnamed: C15.1, CR8.2 (A), R115.2
unnamed: C16.2, CR8.1 (K), Q29.1 (B), R50.1, R122.1
unnamed: Q24.1 (B), R41.1, R111.2, R112.2
unnamed: Q24.3 (C), R42.2, R113.1
unnamed: Q25.1 (B), R43.1, R113.2, R114.2
unnamed: Q26.1 (B), R45.1, R116.2, R117.2
unnamed: Q26.3 (C), R46.2, R118.1
unnamed: Q27.1 (B), R47.1, R118.2, R119.2
P3: R111.1; also elsewhere on the board
P4: C16.1, Q28.3 (C), R122.2, R124.2; also elsewhere on the board
i: R112.1, R117.1; also elsewhere on the board
~P3: R116.1; also elsewhere on the board
~P4c: R114.1; also elsewhere on the board
~P4d: R119.1; also elsewhere on the board
~P4: C13.2, Q29.3 (C), R121.1, R123.2; also elsewhere on the board
